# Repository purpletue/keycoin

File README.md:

# keycoin
A lottery miner that fits on the keychain.
## Software.
This project currently does NOT have software. it was either ship it without soft or using AI, and im not using AI. If ANYBODY wants to help on this project, i'd be grateful to the moon.
## Features!
- An MCU
- A USB-C port
- SWD header
- to be honest there arent many features its all in the soft
## Repository index
- The root has the README, [LICENSE](LICENSE), and PCB files.
## Screenshots

## AI usage declaration
I always put this in my projects. I didnt use AI in this one at all. not even for guidance, which is what i usually do.
## License and date
Made by Yuri Yermol. This project is licensed under the GNU General Public License v.3.0. This document was last modified on 14/11/2026 European format.

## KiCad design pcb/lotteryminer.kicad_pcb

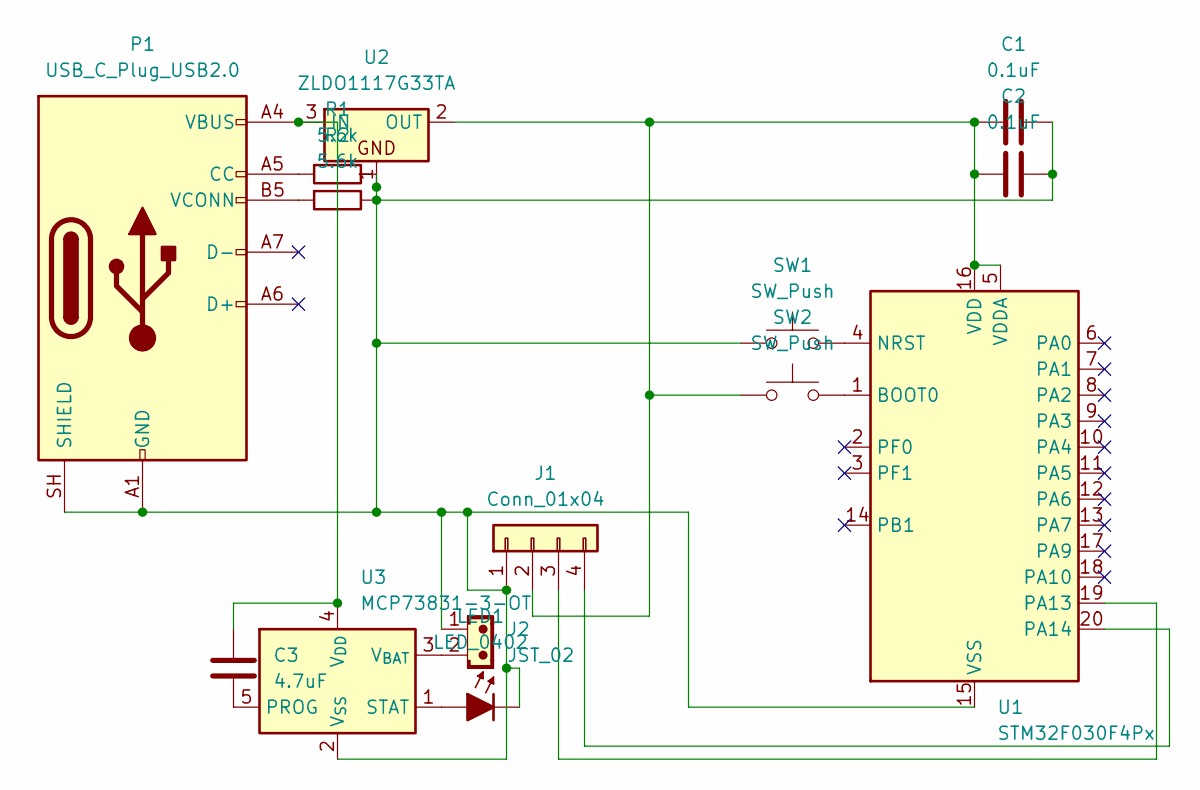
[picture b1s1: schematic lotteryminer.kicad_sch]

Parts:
C1, C2: 0.1uF; C_0201_0603Metric_Pad0.64x0.40mm_HandSolder
C3: 4.7uF; C_0402_1005Metric_Pad0.74x0.62mm_HandSolder
J1: Conn_01x04; PinHeader_1x04_P2.54mm_Vertical_SMD_Pin1Left
J2: JST_02; JST_ZH_B2B-ZR_1x02_P1.50mm_Vertical
LED1: LED_0402; LED_0402_1005Metric
P1: USB_C_Plug_USB2.0; USB_C_Receptacle_Amphenol_124019772112A
R1, R2: 5.6k; R_0201_0603Metric
SW1, SW2: SW_Push; SW_Tactile_SPST_NO_Straight_CK_PTS636Sx25SMTRLFS
U1: STM32F030F4Px; TSSOP-20_4.4x6.5mm_P0.65mm
U2: ZLDO1117G33TA; SOT-223-3_TabPin2
U3: MCP73831-3-OT; SOT-23-5

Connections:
unnamed: C1.2, C2.2, J1.1, J2.1, LED1.1 (K), P1.A1 (GND), P1.A12 (GND), P1.B1 (GND), P1.B12 (GND), P1.SH (SHIELD), R1.2, R2.2, SW1.1, U1.15 (VSS), U2.1, U3.2 (V_{SS})
unnamed: C1.1, C2.1, J1.2, SW2.1, U1.5 (VDDA), U1.16 (VDD), U2.2 (OUT)
unnamed: J1.3, U1.19 (PA13)
unnamed: J1.4, U1.20 (PA14)
unnamed: LED1.2 (A), U3.1 (STAT)
unnamed: P1.A5 (CC), R1.1
unnamed: P1.B5 (VCONN), R2.1
unnamed: SW2.2, U1.1 (BOOT0)
unnamed: SW1.2, U1.4 (NRST)
unnamed: C3.2, P1.A4 (VBUS), P1.A9 (VBUS), P1.B4 (VBUS), P1.B9 (VBUS), U2.3 (IN), U3.4 (V_{DD})
unnamed: C3.1, U3.5 (PROG)
unnamed: J2.2, U3.3 (V_{BAT})

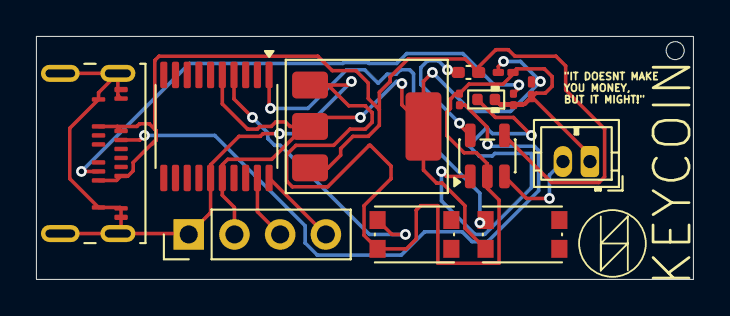
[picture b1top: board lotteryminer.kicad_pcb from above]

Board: 2 copper layers, 36.5 x 13.5 mm, 14 parts (0 on the bottom side), 12 nets.

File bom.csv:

Designator,Footprint,Quantity,Value,LCSC Part #
"C1, C2",0201,2,0.1uF,
C3,0402,1,4.7uF,
J1,PinHeader_1x04_P2.54mm_Vertical,1,Conn_01x04,
J2,JST_ZH_B2B-ZR_1x02_P1.50mm_Vertical,1,JST_02,
LED1,0402,1,LED_0402,
P1,USB_C_Receptacle_Amphenol_124019772112A,1,USB_C_Plug_USB2.0,
"R1, R2",0201,2,5.6k,
"SW1, SW2",SW_Push_1P1T_NO_CK_KMR2,2,SW_Push,
U1,TSSOP-20_4.4x6.5mm_P0.65mm,1,STM32F030F4Px,
U2,SOT-223-3_TabPin2,1,ZLDO1117G33TA,
U3,SOT-23-5,1,MCP73831-3-OT,
